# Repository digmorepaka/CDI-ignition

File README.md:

# CDI-ignition
Basic CDI board with a voltage doubler. 
Connects directly to a Jawa/Babetta 207/210, can also be used with pretty much any high voltage stator and VR sensor.

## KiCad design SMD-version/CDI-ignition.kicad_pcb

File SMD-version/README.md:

## SMD verison with an M6 mounting hole

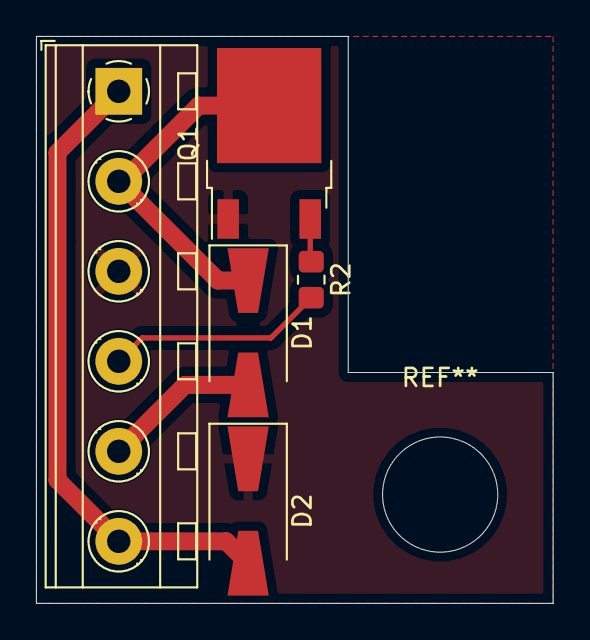
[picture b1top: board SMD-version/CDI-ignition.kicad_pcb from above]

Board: 2 copper layers, 28.7 x 31.5 mm, 5 parts (0 on the bottom side), 6 nets.

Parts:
D1, D2: 1N4007; D_SMA-SMB_Universal_Handsoldering
J1: Screw_Terminal_01x06; TerminalBlock_MetzConnect_Type094_RT03506HBLU_1x06_P5.00mm_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
Q1: BT151; TO-252-2
R2: 180R; R_0805_2012Metric_Pad1.20x1.40mm_HandSolder

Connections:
1: D2.1, J1.3, Q1.1
15: D2.2, J1.1, J1.6
C1: D1.1, J1.2, Q1.2
G: D1.2, J1.5
I: J1.4, R2.2
unnamed: Q1.3, R2.1

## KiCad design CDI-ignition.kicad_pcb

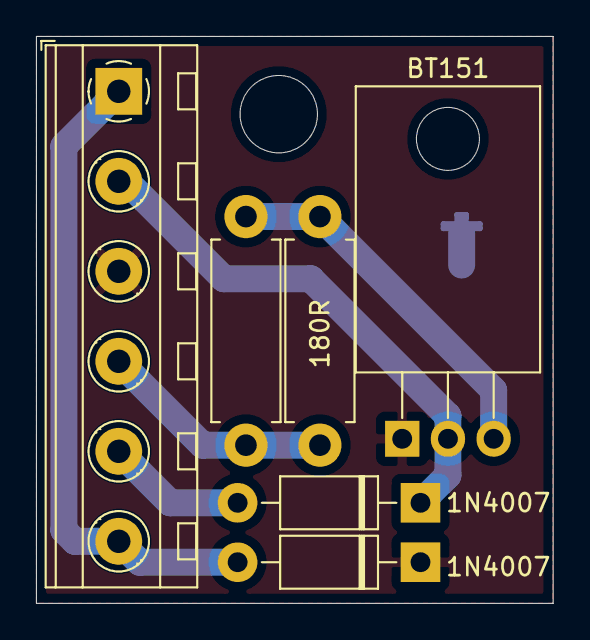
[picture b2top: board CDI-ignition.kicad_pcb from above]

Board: 2 copper layers, 28.7 x 31.5 mm, 6 parts (0 on the bottom side), 6 nets.

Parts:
1N4007, 1N4007#2: 1N4007; D_DO-41_SOD81_P10.16mm_Horizontal
180R: 180R; R_Axial_DIN0411_L9.9mm_D3.6mm_P12.70mm_Horizontal
BT151: X0202MN; TO-220-3_Horizontal_TabDown
J1: Screw_Terminal_01x06; TerminalBlock_MetzConnect_Type094_RT03506HBLU_1x06_P5.00mm_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
R1: placeholder; R_Axial_DIN0411_L9.9mm_D3.6mm_P12.70mm_Horizontal

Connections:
1: 1N4007.1, BT151.1, J1.3
15: 1N4007.2, J1.1, J1.6
C1: 1N4007#2.1, BT151.2, J1.2
G: 1N4007#2.2, J1.5
I: 180R.2, J1.4, R1.2
unnamed: 180R.1, BT151.3, R1.1

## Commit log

2024-01-23 Improve readability
